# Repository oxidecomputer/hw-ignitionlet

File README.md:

# hw-ignitionlet
Breakout board for the ice40 FPGA with SPI PMOD interface

# Bonus boards
There is a lvds_sma_adaptor included which breaks out the LVDS pairs
with a compatible pinout to the [Lattice ECP5 Dev Kit](https://www.latticesemi.com/products/developmentboardsandkits/ecp5evaluationboard)

# Status
No known required rework. See schematic notes for required
jumper settings.

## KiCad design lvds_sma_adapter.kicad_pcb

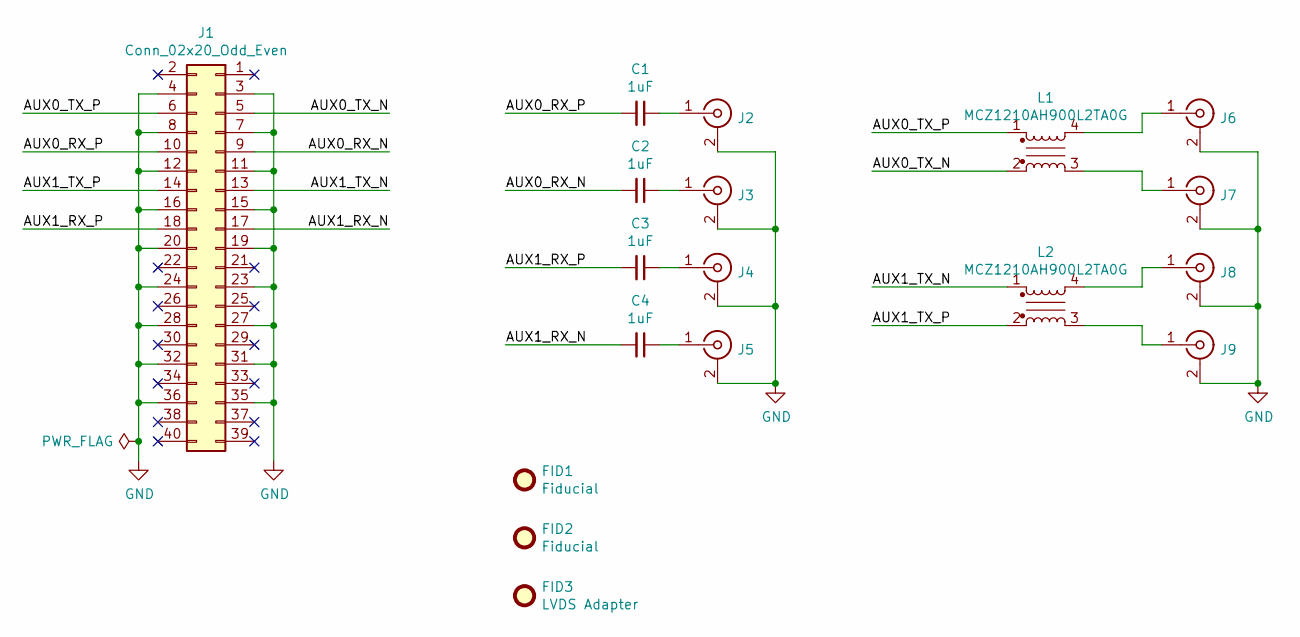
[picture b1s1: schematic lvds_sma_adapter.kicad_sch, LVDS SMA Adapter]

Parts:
C1, C2, C3, C4: GCM188R71E105KA64D; C_0603_1608Metric
FID1, FID2: Fiducial; Fiducial_1mm_Mask2mm
FID3: LVDS Adapter; Oxide_Board_Identifier_23x6mm
J1: Conn_02x20_Odd_Even; PinSocket_2x20_P2.54mm_Horizontal
J2, J3, J4, J5, J6, J7, J8, J9: Conn_Coaxial; SMA_Amphenol_132134-16_Vertical
L1, L2: MCZ1210AH900L2TA0G; L_Choke_MCZ1210AH

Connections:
/AUX0_RX_N: C2.2, J1.9
/AUX0_RX_P: C1.2, J1.10
/AUX0_TX_N: J1.5, L1.2
/AUX0_TX_P: J1.6, L1.1
/AUX1_RX_N: C4.2, J1.17
/AUX1_RX_P: C3.2, J1.18
/AUX1_TX_N: J1.13, L2.1
/AUX1_TX_P: J1.14, L2.2
GND: J1.3, J1.4, J1.7, J1.8, J1.11, J1.12, J1.15, J1.16, J1.19, J1.20, J1.23, J1.24, J1.27, J1.28, J1.31, J1.32, J1.35, J1.36, J2.2 (Ext), J3.2 (Ext), J4.2 (Ext), J5.2 (Ext), J6.2 (Ext), J7.2 (Ext), J8.2 (Ext), J9.2 (Ext)
unnamed: C1.1, J2.1 (In)
unnamed: C2.1, J3.1 (In)
unnamed: C3.1, J4.1 (In)
unnamed: C4.1, J5.1 (In)
unnamed: J6.1 (In), L1.4
unnamed: J7.1 (In), L1.3
unnamed: J8.1 (In), L2.4
unnamed: J9.1 (In), L2.3

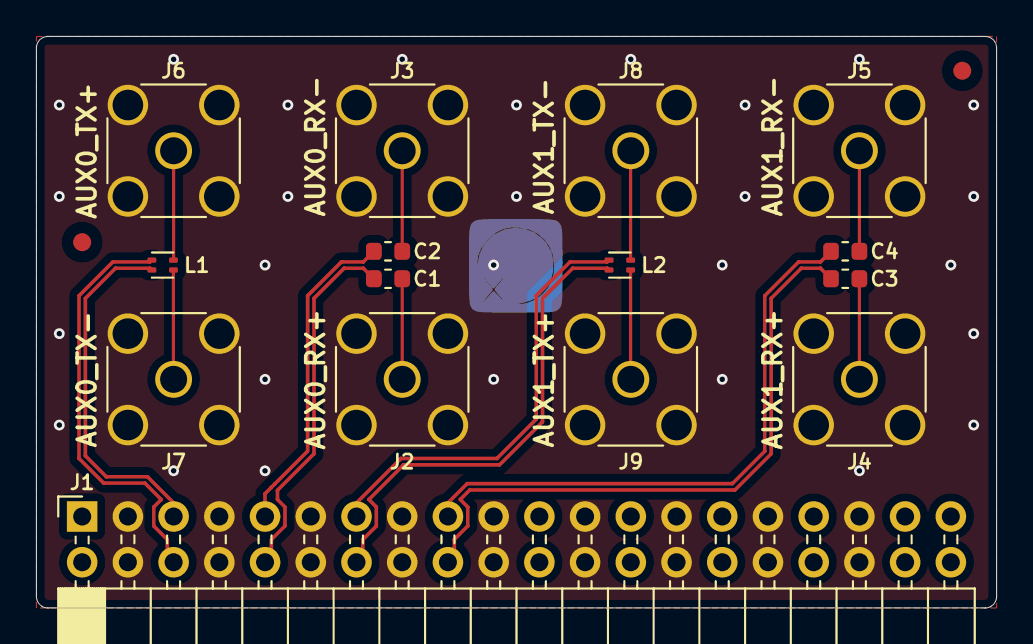
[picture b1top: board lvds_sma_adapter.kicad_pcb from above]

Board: 4 copper layers, 53.3 x 31.8 mm, 18 parts (1 on the bottom side), 17 nets.

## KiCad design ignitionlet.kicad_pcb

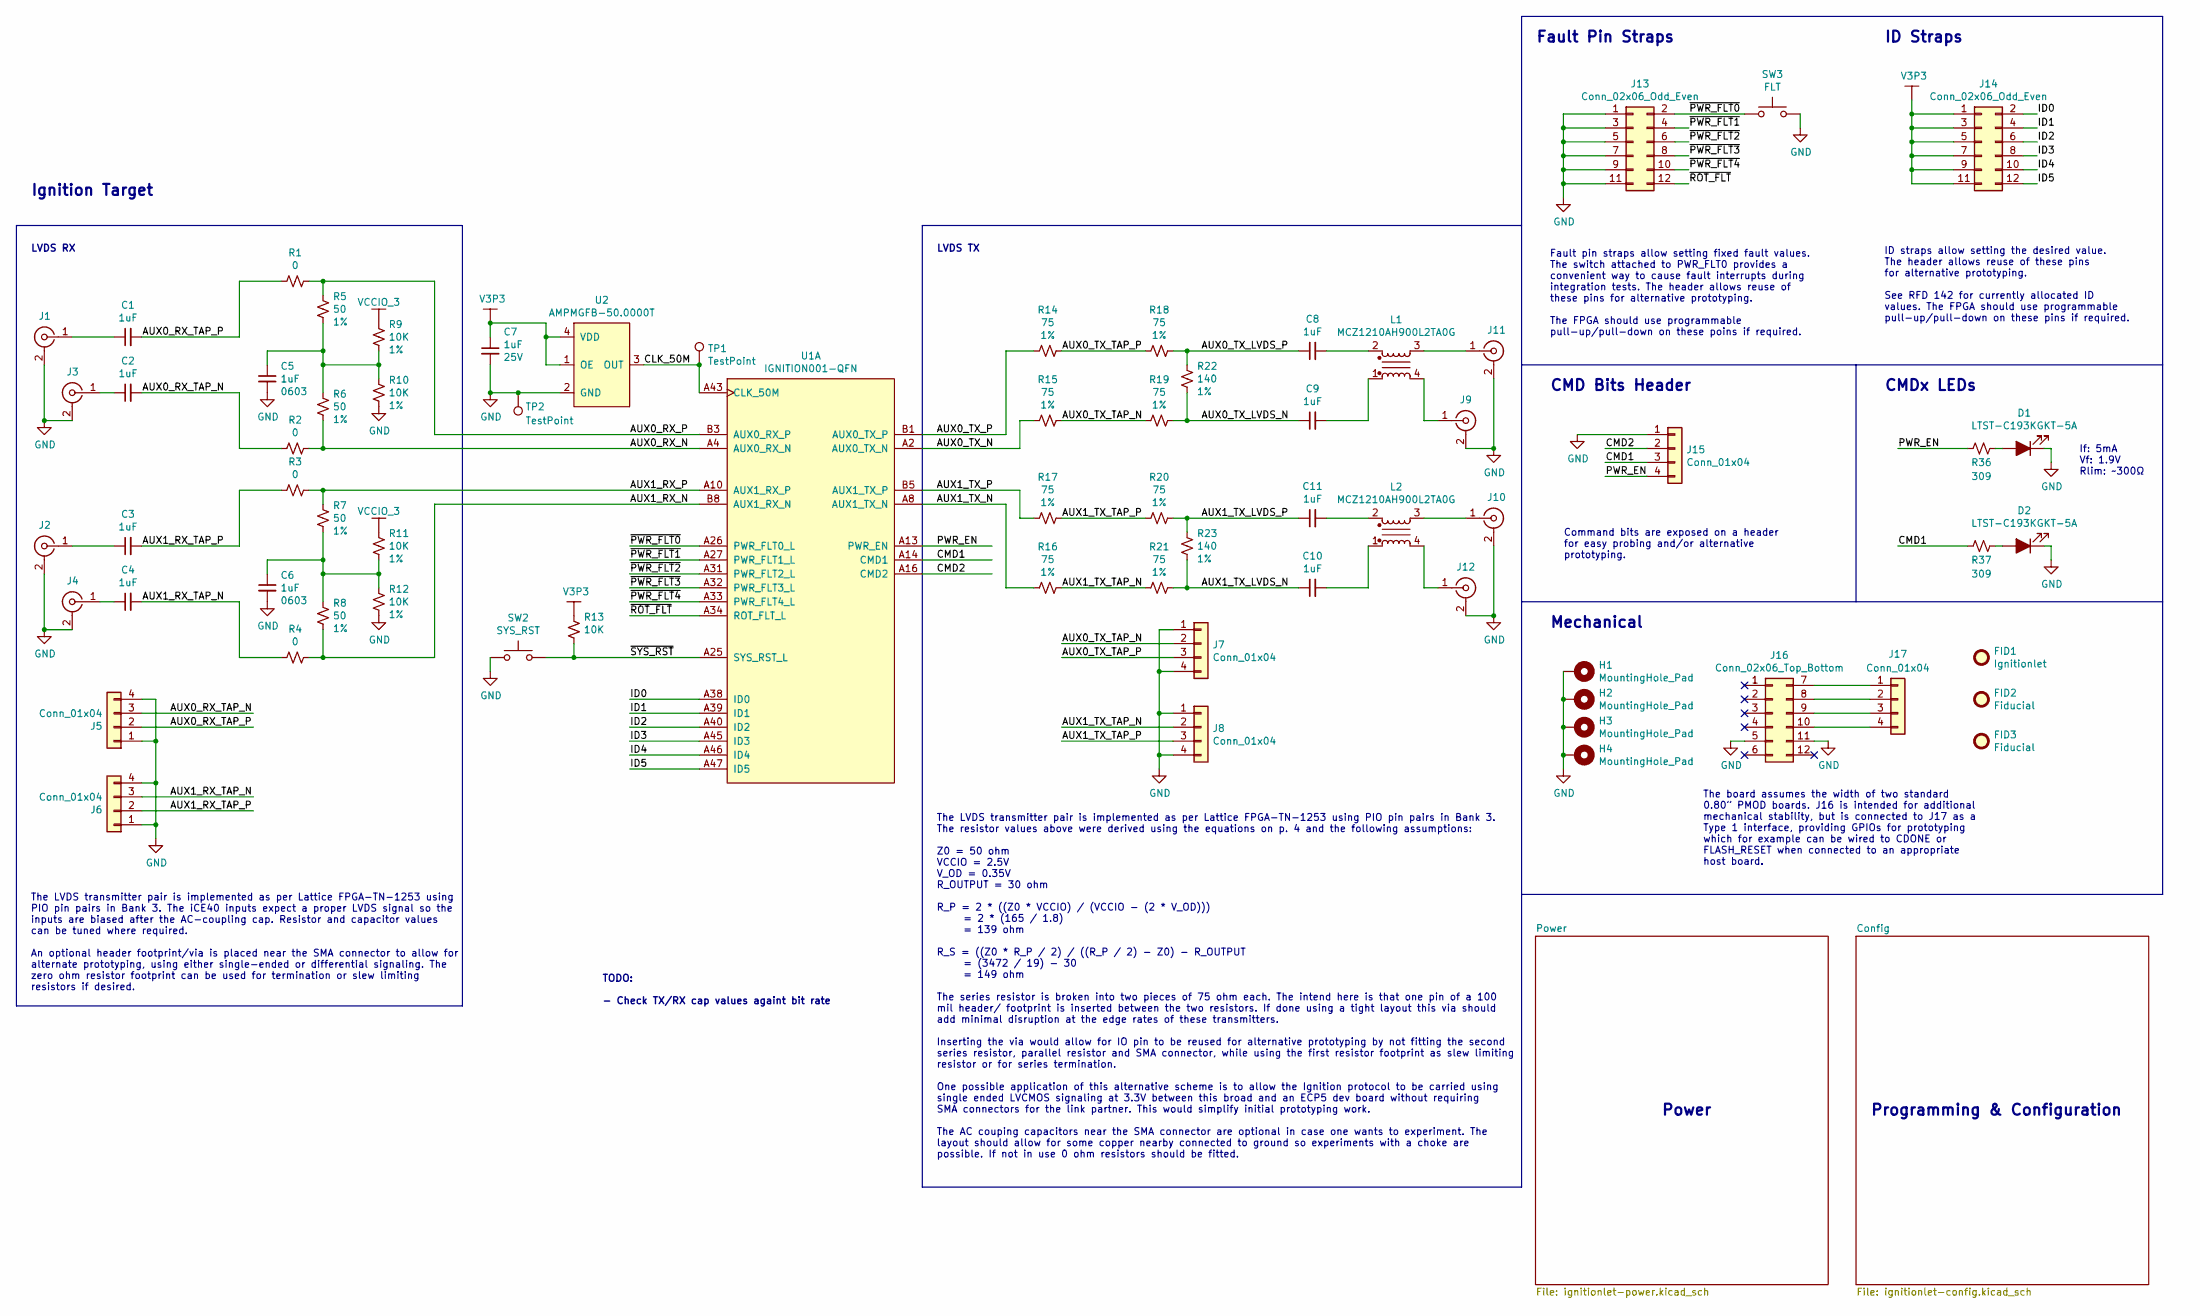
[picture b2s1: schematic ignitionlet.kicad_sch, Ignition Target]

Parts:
C1, C2, C3, C4, C5, C6, C7, C8, C9, C10, C11: GCM188R71E105KA64D; C_0603_1608Metric
D1, D2: LTST-C193KGKT-5A; LED_0603_1608Metric
FID1: Ignitionlet; Oxide_Board_Identifier_23x6mm_PCBWay
FID2, FID3: Fiducial; Fiducial_1mm_Mask2mm
H1, H2, H3, H4: MountingHole_Pad; MountingHole_3.2mm_M3_Pad_Via
J1, J2, J3, J4, J9, J10, J11, J12: Conn_Coaxial; SMA_Amphenol_132134-16_Vertical
J5, J6, J7, J8: Conn_01x04; PinHeader_1x04_P2.54mm_Vertical_SMD_Pin1Left
J13, J14: Conn_02x06_Odd_Even; PinHeader_2x06_P2.54mm_Vertical
J15, J17: Conn_01x04; PinHeader_1x04_P2.54mm_Vertical
J16: Conn_02x06_Top_Bottom; PMOD_12pin_peripheral_horizontal
L1, L2: MCZ1210AH900L2TA0G; L_Choke_MCZ1210AH
R1, R2, R3, R4: 0; R_0603_1608Metric; Tolerance 1%
R5, R6, R7, R8: 50; R_0603_1608Metric; Tolerance 1%
R9, R10, R11, R12, R13: 10K; R_0603_1608Metric; Tolerance 1%
R14, R15, R16, R17, R18, R19, R20, R21: 75; R_0603_1608Metric; Tolerance 1%
R22, R23: 140; R_0603_1608Metric; Tolerance 1%
R36, R37: 309; R_0603_1608Metric; Tolerance 1%
SW2: SYS_RST; PTS815
SW3: FLT; PTS815
TP1: TestPoint; TestPoint_Pad_D0.6mm
TP2: TestPoint; TestPoint_THTPad_D0.6mm_Drill0.3mm
U1: IGNITION001-QFN; Lattice_DRQFN-84-1EP_7x7mm_P0.50mm_EP3.5x3.5mm_ThermalVias
U2: AMPMGFB-50.0000T; ABRACON_VFLGA-4_1.6x1.2mm

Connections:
/AUX0_RX_N: R2.1, R6.2, U1.A4 (AUX0_RX_N)
/AUX0_RX_P: R1.1, R5.1, U1.B3 (AUX0_RX_P)
/AUX0_RX_TAP_N: C2.2, J5.3, R2.2
/AUX0_RX_TAP_P: C1.2, J5.2, R1.2
/AUX0_TX_LVDS_N: C9.1, R19.1, R22.1
/AUX0_TX_LVDS_P: C8.1, R18.1, R22.2
/AUX0_TX_N: R15.2, U1.A2 (AUX0_TX_N)
/AUX0_TX_P: R14.2, U1.B1 (AUX0_TX_P)
/AUX0_TX_TAP_N: J7.2, R15.1, R19.2
/AUX0_TX_TAP_P: J7.3, R14.1, R18.2
/AUX1_RX_N: R4.1, R8.2, U1.B8 (AUX1_RX_N)
/AUX1_RX_P: R3.1, R7.1, U1.A10 (AUX1_RX_P)
/AUX1_RX_TAP_N: C4.2, J6.3, R4.2
/AUX1_RX_TAP_P: C3.2, J6.2, R3.2
/AUX1_TX_LVDS_N: C10.1, R21.1, R23.1
/AUX1_TX_LVDS_P: C11.1, R20.1, R23.2
/AUX1_TX_N: R16.2, U1.A8 (AUX1_TX_N)
/AUX1_TX_P: R17.2, U1.B5 (AUX1_TX_P)
/AUX1_TX_TAP_N: J8.2, R16.1, R21.2
/AUX1_TX_TAP_P: J8.3, R17.1, R20.2
/CLK_50M: TP1.1, U1.A43 (CLK_50M), U2.3 (OUT)
/CMD1: J15.3, R37.2, U1.A14 (CMD1)
/CMD2: J15.2, U1.A16 (CMD2)
/ID0: J14.2, U1.A38 (ID0)
/ID1: J14.4, U1.A39 (ID1)
/ID2: J14.6, U1.A40 (ID2)
/ID3: J14.8, U1.A45 (ID3)
/ID4: J14.10, U1.A46 (ID4)
/ID5: J14.12, U1.A47 (ID5)
/PWR_EN: J15.4, R36.2, U1.A13 (PWR_EN)
/~PWR_FLT0: J13.2, SW3.1, U1.A26 (PWR_FLT0_L)
/~PWR_FLT1: J13.4, U1.A27 (PWR_FLT1_L)
/~PWR_FLT2: J13.6, U1.A31 (PWR_FLT2_L)
/~PWR_FLT3: J13.8, U1.A32 (PWR_FLT3_L)
/~PWR_FLT4: J13.10, U1.A33 (PWR_FLT4_L)
/~ROT_FLT: J13.12, U1.A34 (ROT_FLT_L)
/~SYS_RST: R13.2, SW2.2, U1.A25 (SYS_RST_L)
GND: C5.2, C6.2, C7.2, D1.1 (K), D2.1 (K), H1.1, H2.1, H3.1, H4.1, J1.2 (Ext), J2.2 (Ext), J3.2 (Ext), J4.2 (Ext), J5.1, J5.4, J6.1, J6.4, J7.1, J7.4, J8.1, J8.4, J9.2 (Ext), J10.2 (Ext), J11.2 (Ext), J12.2 (Ext), J13.1, J13.3, J13.5, J13.7, J13.9, J13.11, J15.1, J16.5, J16.11, R10.2, R12.2, SW2.1, SW3.2, TP2.1, U2.2 (GND); also elsewhere on the board
unnamed: C1.1, J1.1 (In)
unnamed: C2.1, J3.1 (In)
unnamed: C3.1, J2.1 (In)
unnamed: C4.1, J4.1 (In)
unnamed: C5.1, R5.2, R6.1, R9.2, R10.1
unnamed: C6.1, R7.2, R8.1, R11.2, R12.1
unnamed: C8.2, L1.2
unnamed: C9.2, L1.1
unnamed: C10.2, L2.1
unnamed: C11.2, L2.2
unnamed: D1.2 (A), R36.1
unnamed: D2.2 (A), R37.1
unnamed: J9.1 (In), L1.4
unnamed: J10.1 (In), L2.3
unnamed: J11.1 (In), L1.3
unnamed: J12.1 (In), L2.4
unnamed: J16.7, J17.1
unnamed: J16.8, J17.2
unnamed: J16.9, J17.3
unnamed: J16.10, J17.4
V3P3: C7.1, J14.1, J14.3, J14.5, J14.7, J14.9, J14.11, R13.1, U2.1 (OE), U2.4 (VDD); also elsewhere on the board
VCCIO_3: R9.1, R11.1; also elsewhere on the board

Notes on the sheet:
CMDx LEDs
The board assumes the width of two standard 0.80” PMOD boards. J16 is intended for additional mechanical stability, but is connected to J17 as a Type 1 interface, providing GPIOs for prototyping which for example can be wired to CDONE or FLASH_RESET when connected to an appropriate host board.
LVDS TX
Ignition Target
Mechanical
Fault Pin Straps
Command bits are exposed on a header for easy probing and/or alternative prototyping.
The LVDS transmitter pair is implemented as per Lattice FPGA-TN-1253 using PIO pin pairs in Bank 3. The resistor values above were derived using the equations on p. 4 and the following assumptions: Z0 = 50 ohm VCCIO = 2.5V V_OD = 0.35V R_OUTPUT = 30 ohm R_P = 2 * ((Z0 * VCCIO) / (VCCIO - (2 * V_OD)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
LVDS RX
ID Straps
CMD Bits Header
Fault pin straps allow setting fixed fault values. The switch attached to PWR_FLT0 provides a convenient way to cause fault interrupts during integration tests. The header allows reuse of these pins for alternative prototyping. The FPGA should use programmable pull-up/pull-down on these poins if re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
Programming & Configuration
The LVDS transmitter pair is implemented as per Lattice FPGA-TN-1253 using PIO pin pairs in Bank 3. The iCE40 inputs expect a proper LVDS signal so the inputs are biased after the AC-coupling cap. Resistor and capacitor values can be tuned where required. An optional header footprint/via is placed 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
ID straps allow setting the desired value. The header allows reuse of these pins for alternative prototyping. See RFD 142 for currently allocated ID values. The FPGA should use programmable pull-up/pull-down on these pins if required.
If: 5mA Vf: 1.9V Rlim: ~300Ω
Power
TODO: - Check TX/RX cap values againt bit rate

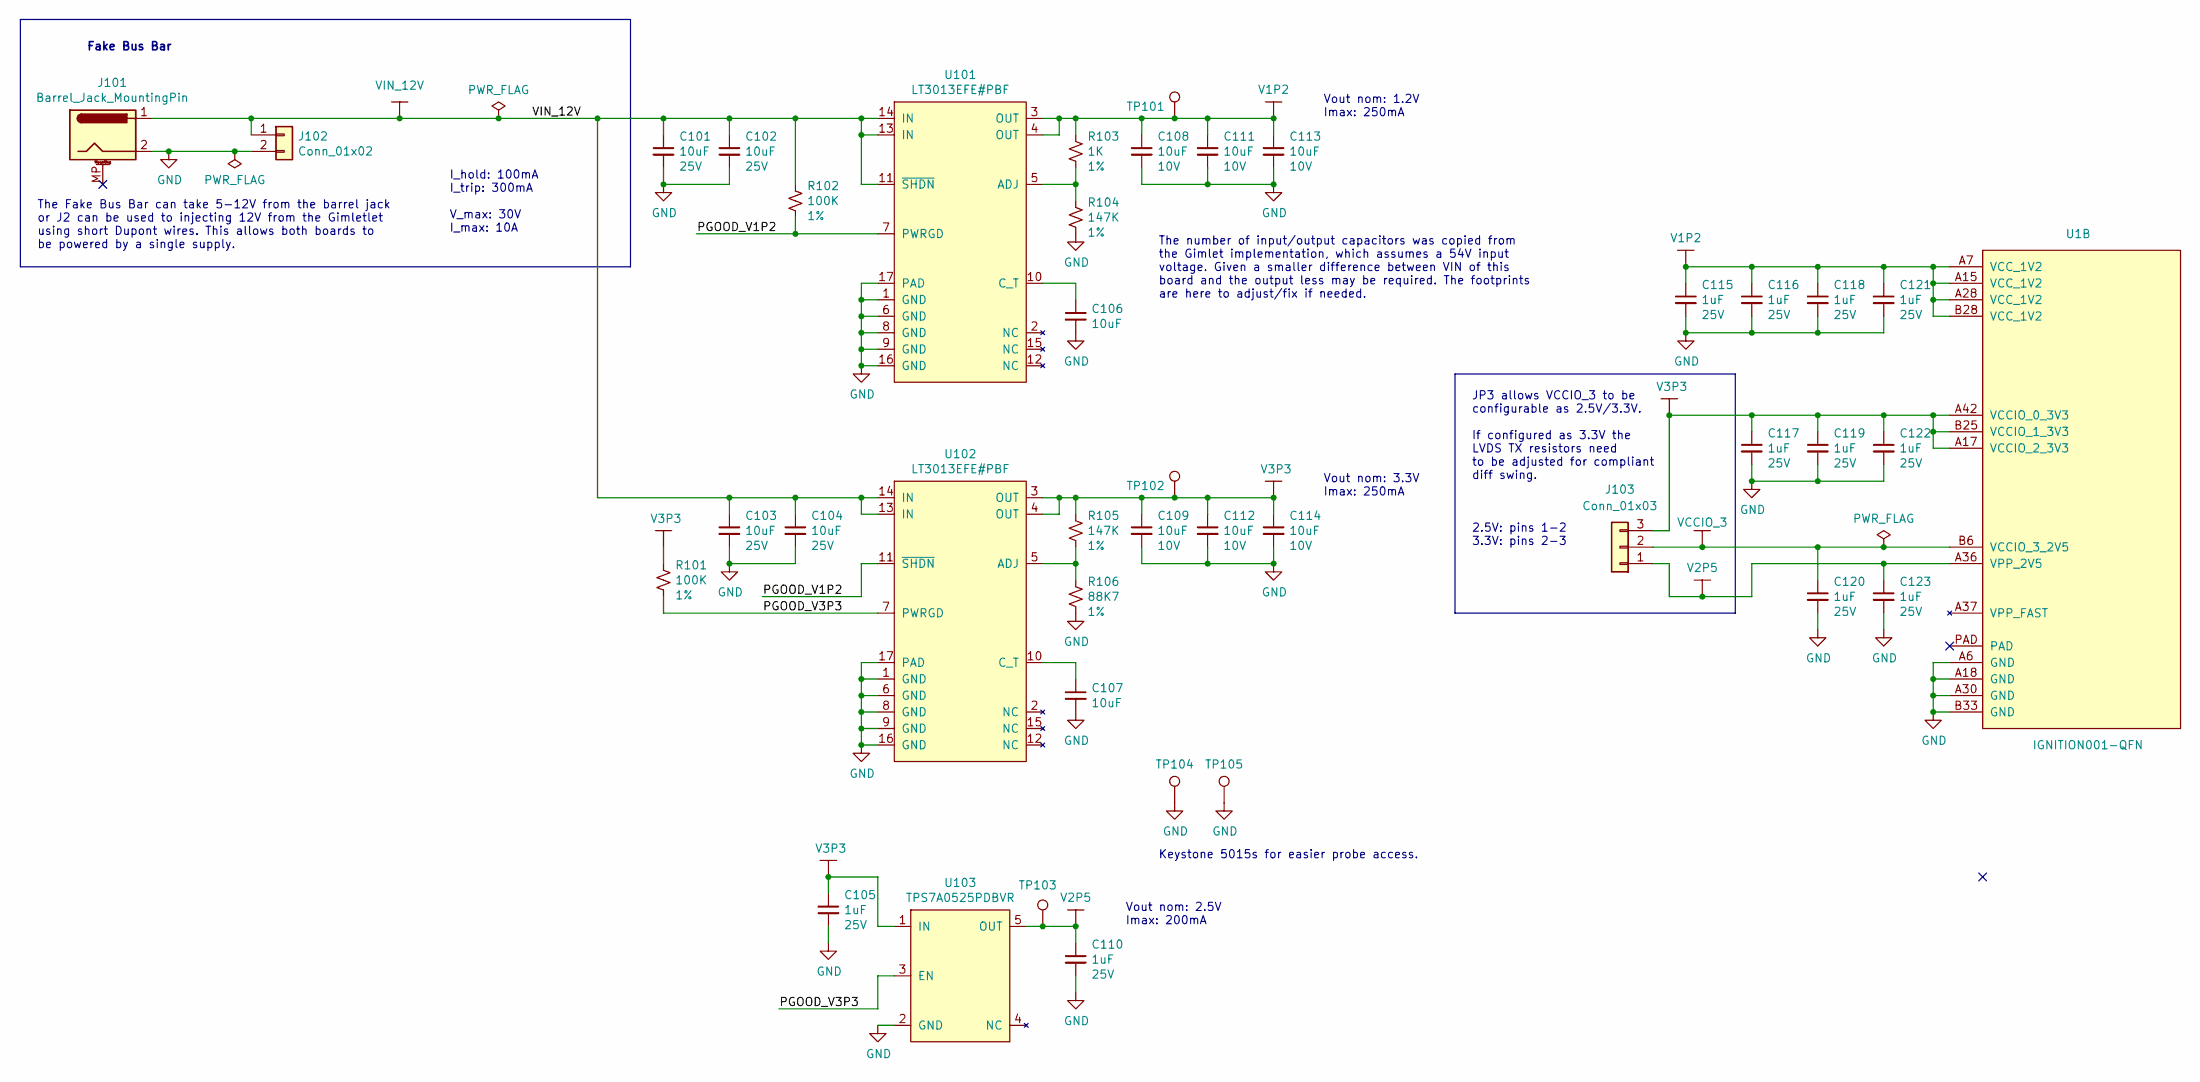
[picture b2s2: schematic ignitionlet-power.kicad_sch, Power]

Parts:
C101, C102, C103, C104: GRM21BR61E106KA73K; C_0805_2012Metric; Voltage 25V
C105, C110, C115, C116, C117, C118, C119, C120, C121, C122, C123: GCM188R71E105KA64D; C_0603_1608Metric
C106, C107: C0603C106M8PACTU; C_0603_1608Metric
C108, C109, C111, C112, C113, C114: C0603C106M8PACTU; C_0603_1608Metric; Voltage 10V
J101: Barrel_Jack_MountingPin; BarrelJack_Horizontal
J102: Conn_01x02; PinHeader_1x02_P2.54mm_Vertical
J103: Conn_01x03; PinHeader_1x03_P2.54mm_Vertical
R101, R102: 100K; R_0603_1608Metric; Tolerance 1%
R103: 1K; R_0603_1608Metric; Tolerance 1%
R104, R105: 147K; R_0603_1608Metric; Tolerance 1%
R106: 88K7; R_0603_1608Metric; Tolerance 1%
TP101, TP102: TestPoint; TestPoint_THTPad_D1.0mm_Drill0.5mm
TP103: TestPoint; TestPoint_Pad_D0.6mm
TP104, TP105: TestPoint; TestPoint_Keystone_5015_Micro-Minature
U1: IGNITION001-QFN
U101, U102: LT3013EFE#PBF; TSSOP-16-1EP_4.4x5mm_P0.65mm
U103: TPS7A0525PDBVR; SOT-23-5

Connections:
/Power/PGOOD_V1P2: R102.2, U101.7 (PWRGD), U102.11 (~SHDN)
/Power/PGOOD_V3P3: R101.2, U102.7 (PWRGD), U103.3 (EN)
GND: C101.2, C102.2, C103.2, C104.2, C105.2, C106.2, C107.2, C108.2, C109.2, C110.2, C111.2, C112.2, C113.2, C114.2, C115.2, C116.2, C117.2, C118.2, C119.2, C120.2, C121.2, C122.2, C123.2, J101.2, J102.2, R104.2, R106.2, TP104.1, TP105.1, U1.A6 (GND), U1.A18 (GND), U1.A30 (GND), U1.B33 (GND), U101.1 (GND), U101.6 (GND), U101.8 (GND), U101.9 (GND), U101.16 (GND), U101.17 (PAD), U102.1 (GND), U102.6 (GND), U102.8 (GND), U102.9 (GND), U102.16 (GND), U102.17 (PAD), U103.2 (GND); also elsewhere on the board
unnamed: C106.1, U101.10 (C_T)
unnamed: C107.1, U102.10 (C_T)
unnamed: R103.2, R104.1, U101.5 (ADJ)
unnamed: R105.2, R106.1, U102.5 (ADJ)
V1P2: C108.1, C111.1, C113.1, C115.1, C116.1, C118.1, C121.1, R103.1, TP101.1, U1.A7 (VCC_1V2), U1.A15 (VCC_1V2), U1.A28 (VCC_1V2), U1.B28 (VCC_1V2), U101.3 (OUT), U101.4 (OUT)
V2P5: C110.1, C123.1, J103.1, TP103.1, U1.A36 (VPP_2V5), U103.5 (OUT)
V3P3: C105.1, C109.1, C112.1, C114.1, C117.1, C119.1, C122.1, J103.3, R101.1, R105.1, TP102.1, U1.A17 (VCCIO_2_3V3), U1.A42 (VCCIO_0_3V3), U1.B25 (VCCIO_1_3V3), U102.3 (OUT), U102.4 (OUT), U103.1 (IN); also elsewhere on the board
VCCIO_3: C120.1, J103.2, U1.B6 (VCCIO_3_2V5); also elsewhere on the board
VIN_12V: C101.1, C102.1, C103.1, C104.1, J101.1, J102.1, R102.1, U101.11 (~SHDN), U101.13 (IN), U101.14 (IN), U102.13 (IN), U102.14 (IN)

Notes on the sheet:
Vout nom: 2.5V Imax: 200mA
Fake Bus Bar
The Fake Bus Bar can take 5-12V from the barrel jack or J2 can be used to injecting 12V from the Gimletlet using short Dupont wires. This allows both boards to be powered by a single supply.
Keystone 5015s for easier probe access.
I_hold: 100mA I_trip: 300mA V_max: 30V I_max: 10A
The number of input/output capacitors was copied from the Gimlet implementation, which assumes a 54V input voltage. Given a smaller difference between VIN of this board and the output less may be required. The footprints are here to adjust/fix if needed.
2.5V: pins 1-2 3.3V: pins 2-3
Vout nom: 1.2V Imax: 250mA
JP3 allows VCCIO_3 to be configurable as 2.5V/3.3V. If configured as 3.3V the LVDS TX resistors need to be adjusted for compliant diff swing.
Vout nom: 3.3V Imax: 250mA

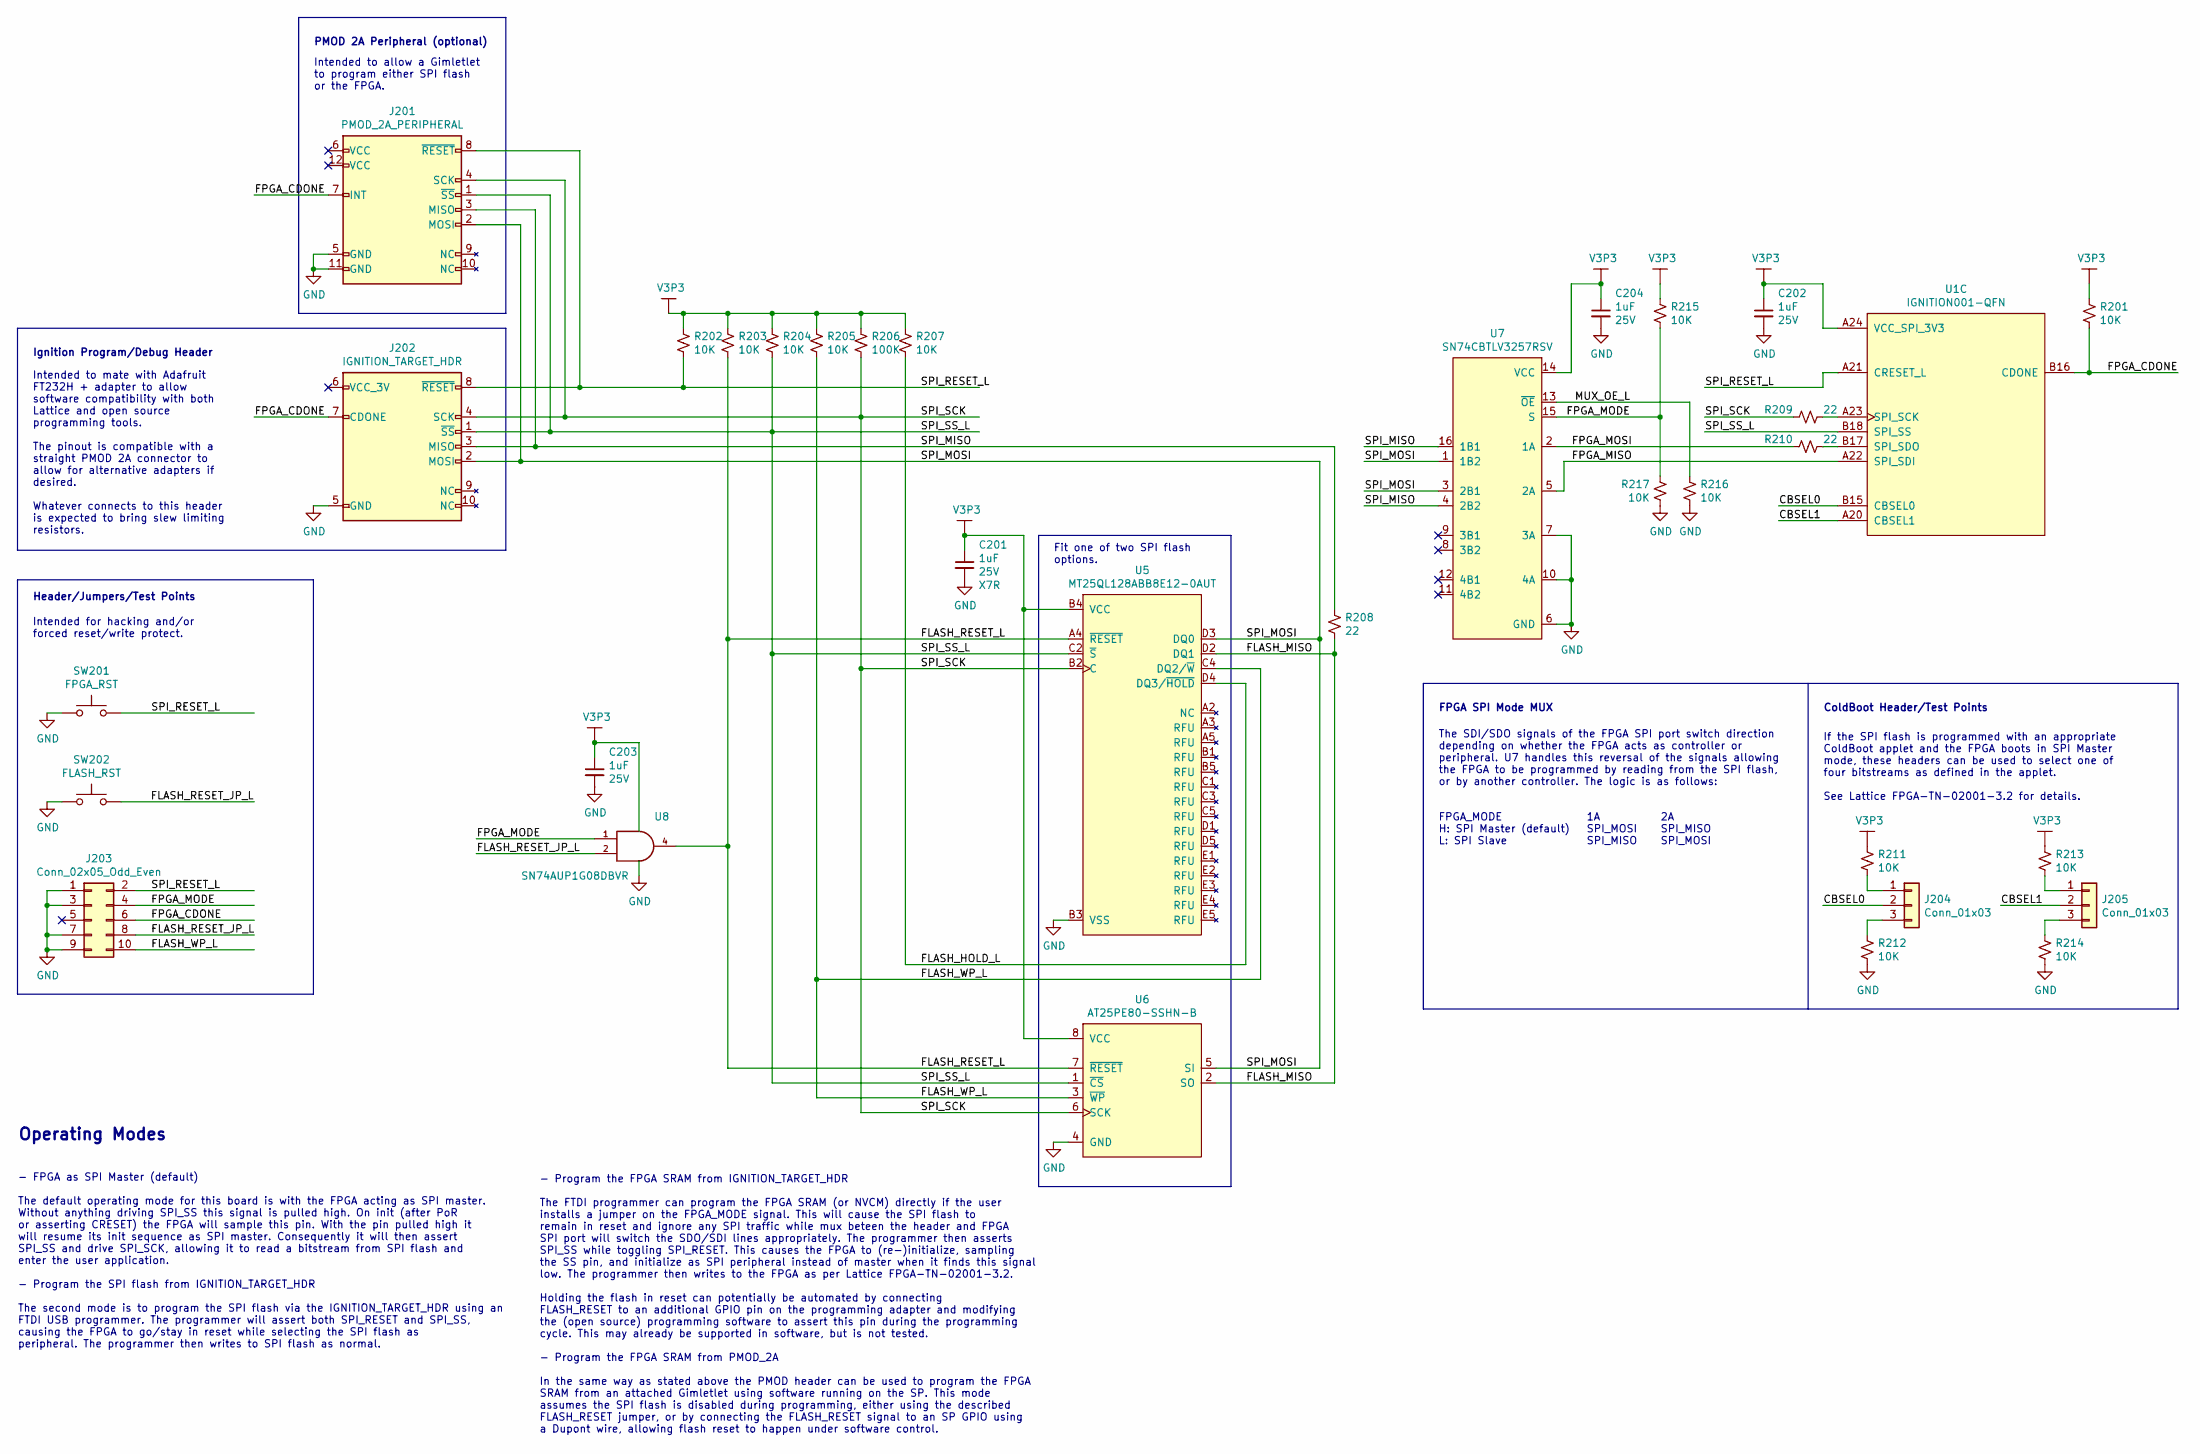
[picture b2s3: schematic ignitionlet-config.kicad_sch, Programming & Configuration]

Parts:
C201, C202, C203, C204: GCM188R71E105KA64D; C_0603_1608Metric
J201: PMOD_2A_PERIPHERAL; PMOD_12pin_peripheral_horizontal
J202: IGNITION_TARGET_HDR; TFC-105-02-F-D-A-K
J203: Conn_02x05_Odd_Even; PinHeader_2x05_P2.54mm_Vertical
J204, J205: Conn_01x03; PinHeader_1x03_P2.54mm_Vertical
R201, R202, R203, R204, R205, R207, R211, R212, R213, R214, R215, R216, R217: 10K; R_0603_1608Metric; Tolerance 1%
R206: 100K; R_0603_1608Metric; Tolerance 1%
R208, R209, R210: 22; R_0603_1608Metric; Tolerance 1%
SW201: FPGA_RST; PTS815
SW202: FLASH_RST; PTS815
U1: IGNITION001-QFN
U5: MT25QL128ABB8E12-0AUT; T-PBGA-24_6x8mm_Layout5x5_P1.0mm
U6: AT25PE80-SSHN-B; SOIC-8_3.9x4.9mm_P1.27mm
U7: SN74CBTLV3257RSV; Texas_RSV_S-UQFN-16_2.4x1.6mm
U8: SN74AUP1G08DBVR; SOT-23-5

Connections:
/Config/CBSEL0: J204.2, U1.B15 (CBSEL0)
/Config/CBSEL1: J205.2, U1.A20 (CBSEL1)
/Config/FLASH_HOLD_L: R207.1, U5.D4 (DQ3/~HOLD)
/Config/FLASH_MISO: R208.1, U5.D2 (DQ1), U6.2 (SO)
/Config/FLASH_RESET_JP_L: J203.8, SW202.2, U8.2
/Config/FLASH_RESET_L: R203.1, U5.A4 (~RESET), U6.7 (~RESET), U8.4
/Config/FLASH_WP_L: J203.10, R205.1, U5.C4 (DQ2/~W), U6.3 (~WP)
/Config/FPGA_CDONE: J201.7 (INT), J202.7 (CDONE), J203.6, R201.1, U1.B16 (CDONE)
/Config/FPGA_MISO: U1.A22 (SPI_SDI), U7.5 (2A)
/Config/FPGA_MODE: J203.4, R215.1, R217.2, U7.15 (S), U8.1
/Config/FPGA_MOSI: R210.2, U7.2 (1A)
/Config/MUX_OE_L: R216.2, U7.13 (~OE)
/Config/SPI_MISO: J201.3 (MISO), J202.3 (MISO), R208.2, U7.4 (2B2), U7.16 (1B1)
/Config/SPI_MOSI: J201.2 (MOSI), J202.2 (MOSI), U5.D3 (DQ0), U6.5 (SI), U7.1 (1B2), U7.3 (2B1)
/Config/SPI_RESET_L: J201.8 (~RESET), J202.8 (~RESET), J203.2, R202.1, SW201.2, U1.A21 (CRESET_L)
/Config/SPI_SCK: J201.4 (SCK), J202.4 (SCK), R206.1, R209.2, U5.B2 (C), U6.6 (SCK)
/Config/SPI_SS_L: J201.1 (~SS), J202.1 (~SS), R204.1, U1.B18 (SPI_SS), U5.C2 (~S), U6.1 (~CS)
GND: C201.2, C202.2, C203.2, C204.2, J201.5 (GND), J201.11 (GND), J202.5 (GND), J203.1, J203.3, J203.7, J203.9, R212.1, R214.1, R216.1, R217.1, SW201.1, SW202.1, U5.B3 (VSS), U6.4 (GND), U7.6 (GND), U7.7 (3A), U7.10 (4A), U8.3 (GND); also elsewhere on the board
unnamed: J204.1, R211.1
unnamed: J204.3, R212.2
unnamed: J205.1, R213.1
unnamed: J205.3, R214.2
unnamed: R209.1, U1.A23 (SPI_SCK)
unnamed: R210.1, U1.B17 (SPI_SDO)
V3P3: C201.1, C202.1, C203.1, C204.1, R201.2, R202.2, R203.2, R204.2, R205.2, R206.2, R207.2, R211.2, R213.2, R215.2, U1.A24 (VCC_SPI_3V3), U5.B4 (VCC), U6.8 (VCC), U7.14 (VCC), U8.5 (VCC); also elsewhere on the board

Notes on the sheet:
Ignition Program/Debug Header
The SDI/SDO signals of the FPGA SPI port switch direction depending on whether the FPGA acts as controller or peripheral. U7 handles this reversal of the signals allowing the FPGA to be programmed by reading from the SPI flash, or by another controller. The logic is as follows:
FPGA_MODE H: SPI Master (default) L: SPI Slave
Fit one of two SPI flash options.
Intended to allow a Gimletlet to program either SPI flash or the FPGA.
Operating Modes
ColdBoot Header/Test Points
Intended for hacking and/or forced reset/write protect.
- Program the FPGA SRAM from IGNITION_TARGET_HDR The FTDI programmer can program the FPGA SRAM (or NVCM) directly if the user installs a jumper on the FPGA_MODE signal. This will cause the SPI flash to remain in reset and ignore any SPI traffic while mux beteen the header and FPGA SPI port will swi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
Header/Jumpers/Test Points
2A SPI_MISO SPI_MOSI
PMOD 2A Peripheral (optional)
Intended to mate with Adafruit FT232H + adapter to allow software compatibility with both Lattice and open source programming tools. The pinout is compatible with a straight PMOD 2A connector to allow for alternative adapters if desired. Whatever connects to this header is expected to bring slew li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
If the SPI flash is programmed with an appropriate ColdBoot applet and the FPGA boots in SPI Master mode, these headers can be used to select one of four bitstreams as defined in the applet. See Lattice FPGA-TN-02001-3.2 for details.
1A SPI_MOSI SPI_MISO
FPGA SPI Mode MUX
- FPGA as SPI Master (default) The default operating mode for this board is with the FPGA acting as SPI master. Without anything driving SPI_SS this signal is pulled high. On init (after PoR or asserting CRESET) the FPGA will sample this pin. With the pin pulled high it will resume its init sequenc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

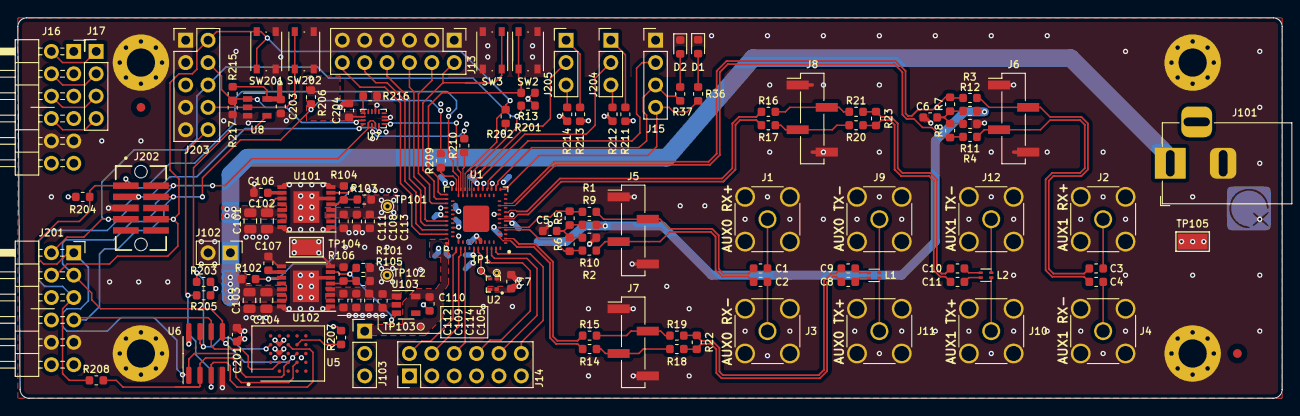
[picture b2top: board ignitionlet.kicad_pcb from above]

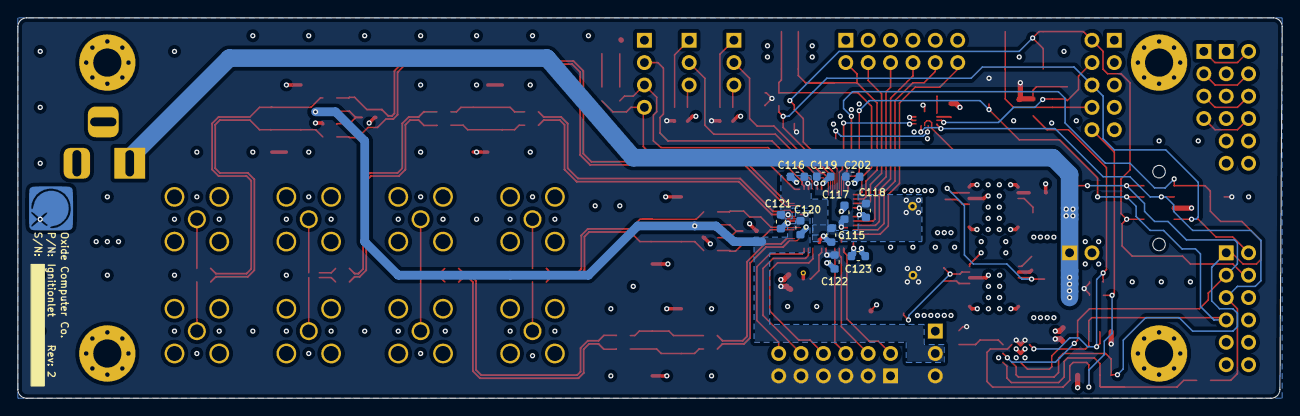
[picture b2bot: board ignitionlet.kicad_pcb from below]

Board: 4 copper layers, 143.5 x 43.2 mm, 142 parts (11 on the bottom side), 92 nets.

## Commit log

2023-02-28 Initial commit after restructure
2023-02-28 Remove pdf, now in Releases
